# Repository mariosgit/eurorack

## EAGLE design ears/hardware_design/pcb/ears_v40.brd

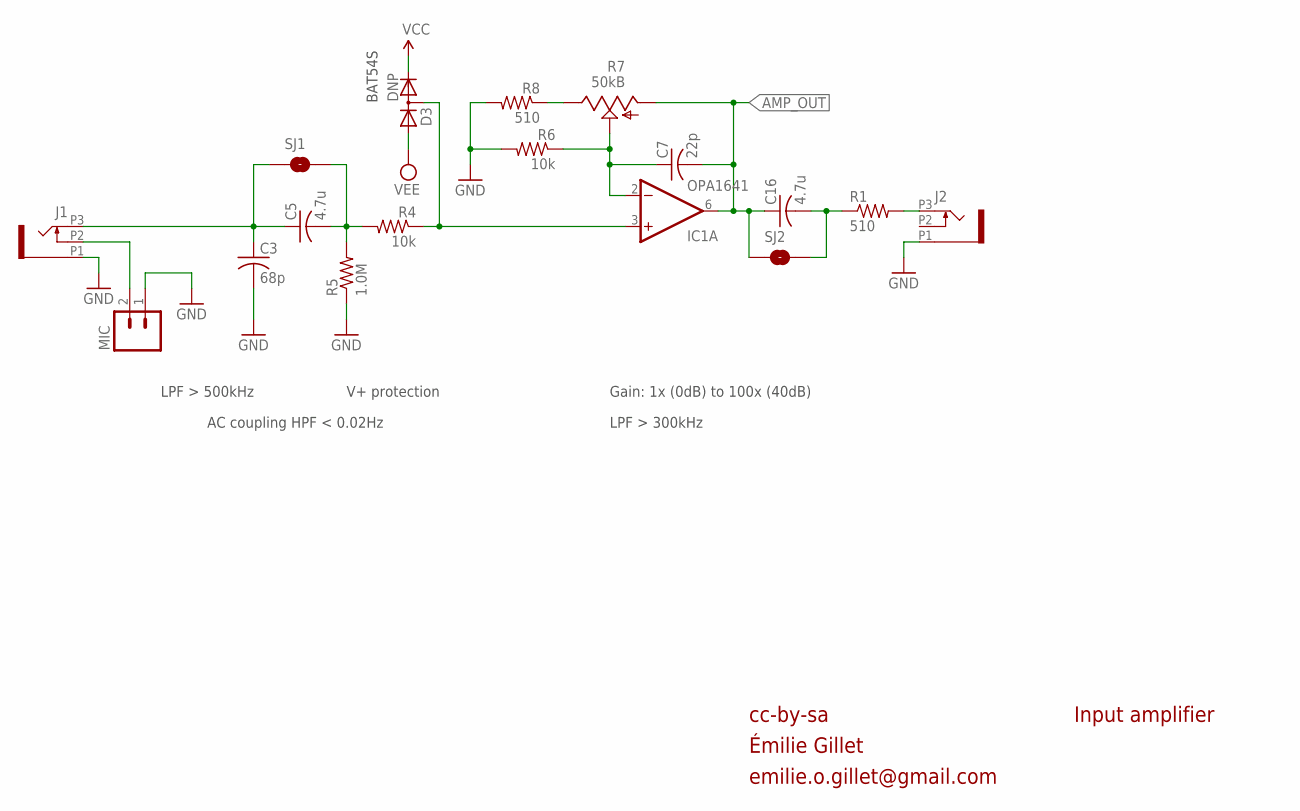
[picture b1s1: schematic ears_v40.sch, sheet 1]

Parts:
C3: 68p; C0402
C5, C16: 4.7u; C0603
C7: 22p; C0402
D3: DNP; SOT23
IC1: OPA1641; MSOP8
J1, J2: PJ301_THONKICONN6; WQP_PJ_301M6
MIC: M02TINY; 1X02_TINY
R1, R8: 510; R0402
R4, R6: 10k; R0402
R5: 1.0M; R0402
R7: 50kB; ALPS_POT_VERTICAL_PS
SJ1, SJ2: SOLDERJUMPERNC; SJ_2S

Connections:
AMP_OUT: C7.2, C16.1, IC1.6 (OUT), R7.P$3 (A), SJ2.1; also elsewhere on the board
GND: C3.2, J1.P1 (1), J2.P1 (1), MIC.1, R5.1, R6.2, R8.2; also elsewhere on the board
unnamed: D3.3 (AC), IC1.3 (+IN), R4.1
unnamed: J2.P3 (3), R1.2
unnamed: C3.1, C5.1, J1.P3 (3), SJ1.1
unnamed: J1.P2 (2), MIC.2
unnamed: C7.1, IC1.2 (-IN), R6.1, R7.P$2 (S)
unnamed: C5.2, R4.2, R5.2, SJ1.2
unnamed: R7.P$1 (E), R8.1
unnamed: C16.2, R1.1, SJ2.2
VCC: D3.2 (C); also elsewhere on the board
VEE: D3.1 (A); also elsewhere on the board

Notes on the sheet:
cc-by-sa
Input amplifier
Gain: 1x (0dB) to 100x (40dB)
LPF > 500kHz
V+ protection
LPF > 300kHz
AC coupling HPF < 0.02Hz
BAT54S
Émilie Gillet
emilie.o.gillet@gmail.com

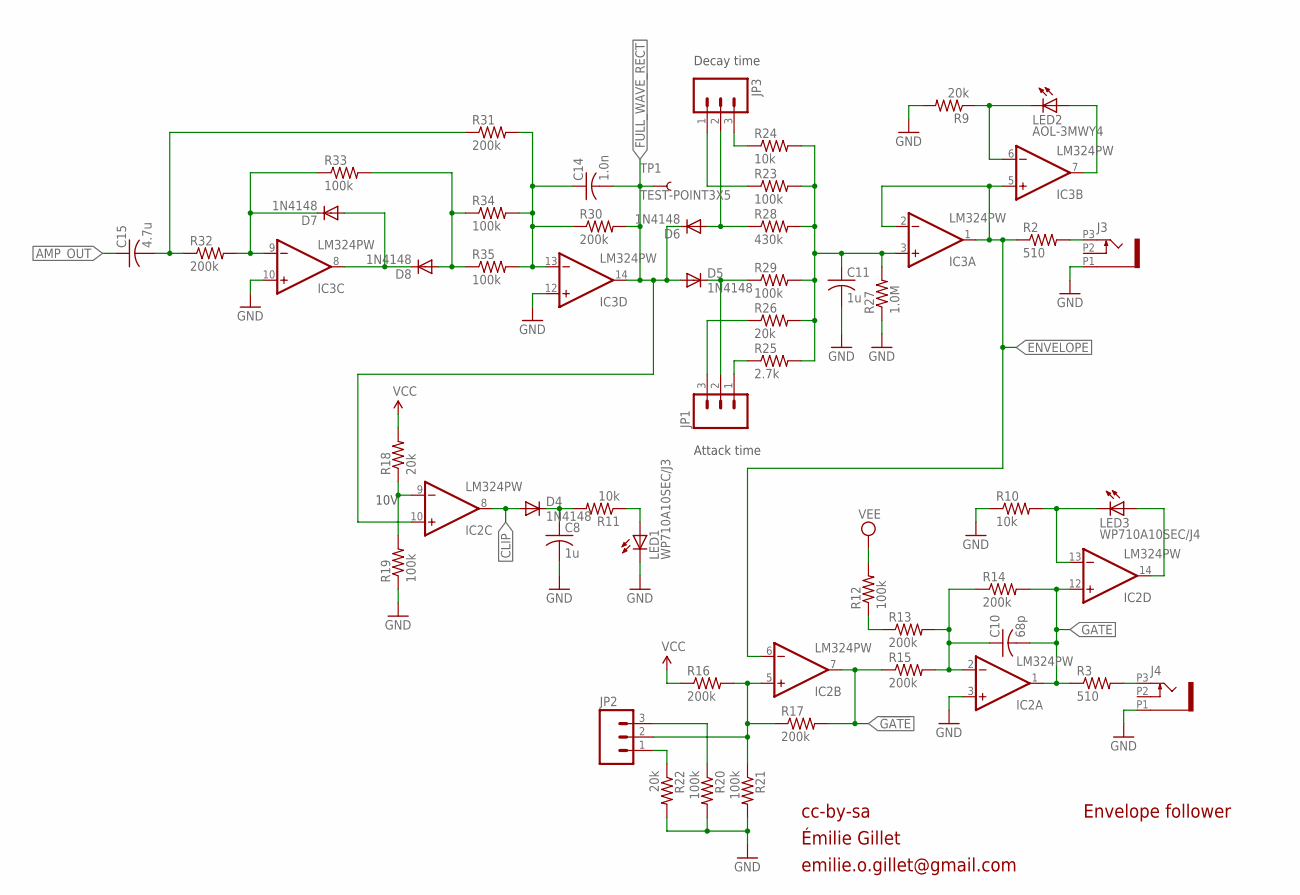
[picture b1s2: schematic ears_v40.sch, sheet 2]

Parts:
C8, C11: 1u; C0402
C10: 68p; C0402
C14: 1.0n; C0402
C15: 4.7u; C0603
D4, D5, D6, D7, D8: 1N4148; SOD523
IC2, IC3: LM324PW; TSSOP14
J3, J4: PJ301_THONKICONN6; WQP_PJ_301M6
JP1, JP2, JP3: M03PTH; 1X03
LED1: WP710A10SEC/J3; LED3MM
LED2: AOL-3MWY4; LED3MM
LED3: WP710A10SEC/J4; LED3MM
R2, R3: 510; R0402
R9, R18, R22, R26: 20k; R0402
R10, R11, R24: 10k; R0402
R12, R19, R20, R21, R23, R29, R33, R34, R35: 100k; R0402
R13, R14, R15, R16, R17, R30, R31, R32: 200k; R0402
R25: 2.7k; R0402
R27: 1.0M; R0402
R28: 430k; R0402
TP1: TEST-POINT3X5; PAD.03X.05

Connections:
!GATE: IC2.7 (OUT), R15.1, R17.2
AMP_OUT: C15.1; also elsewhere on the board
AMP_OUT_AC: C15.2, R31.1, R32.1
CLIP: D4.A, IC2.8 (OUT)
ENVELOPE: IC2.6 (-IN), IC3.1 (OUT), IC3.2 (-IN), IC3.5 (+IN), R2.1
FULL_WAVE_RECT: C14.2, D5.A, D6.C, IC2.10 (+IN), IC3.14 (OUT), R30.2, TP1.P$1
GATE: C10.2, IC2.1 (OUT), IC2.12 (+IN), R3.1, R14.2
GND: C8.2, C11.2, IC2.3 (+IN), IC3.10 (+IN), IC3.12 (+IN), J3.P1 (1), J4.P1 (1), LED1.K (C), R9.2, R10.1, R19.1, R20.2, R21.2, R22.2, R27.1; also elsewhere on the board
unnamed: D7.A, D8.C, IC3.8 (OUT)
unnamed: C10.1, IC2.2 (-IN), R13.2, R14.1, R15.2
unnamed: D7.C, IC3.9 (-IN), R32.2, R33.1
unnamed: D8.A, R33.2, R34.1, R35.1
unnamed: C14.1, IC3.13 (-IN), R30.1, R31.2, R34.2, R35.2
unnamed: J3.P3 (3), R2.2
unnamed: IC3.6 (-IN), LED2.K (C), R9.1
unnamed: D5.C, JP1.2, R29.1
unnamed: C11.1, IC3.3 (+IN), R23.2, R24.2, R25.2, R26.2, R27.2, R28.2, R29.2
unnamed: JP3.3, R24.1
unnamed: JP3.1, R23.1
unnamed: D6.A, JP3.2, R28.1
unnamed: JP1.1, R25.1
unnamed: JP1.3, R26.1
unnamed: IC2.9 (-IN), R18.1, R19.2
unnamed: C8.1, D4.C, R11.2
unnamed: IC3.7 (OUT), LED2.A
unnamed: LED1.A, R11.1
unnamed: J4.P3 (3), R3.2
unnamed: IC2.5 (+IN), JP2.2, R16.2, R17.1, R21.1
unnamed: JP2.1, R22.1
unnamed: JP2.3, R20.1
unnamed: IC2.13 (-IN), LED3.K (C), R10.2
unnamed: IC2.14 (OUT), LED3.A
unnamed: R12.1, R13.1
VCC: R16.1, R18.2; also elsewhere on the board
VEE: R12.2; also elsewhere on the board

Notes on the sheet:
cc-by-sa
Envelope follower
Decay time
Attack time
10V
Émilie Gillet
emilie.o.gillet@gmail.com

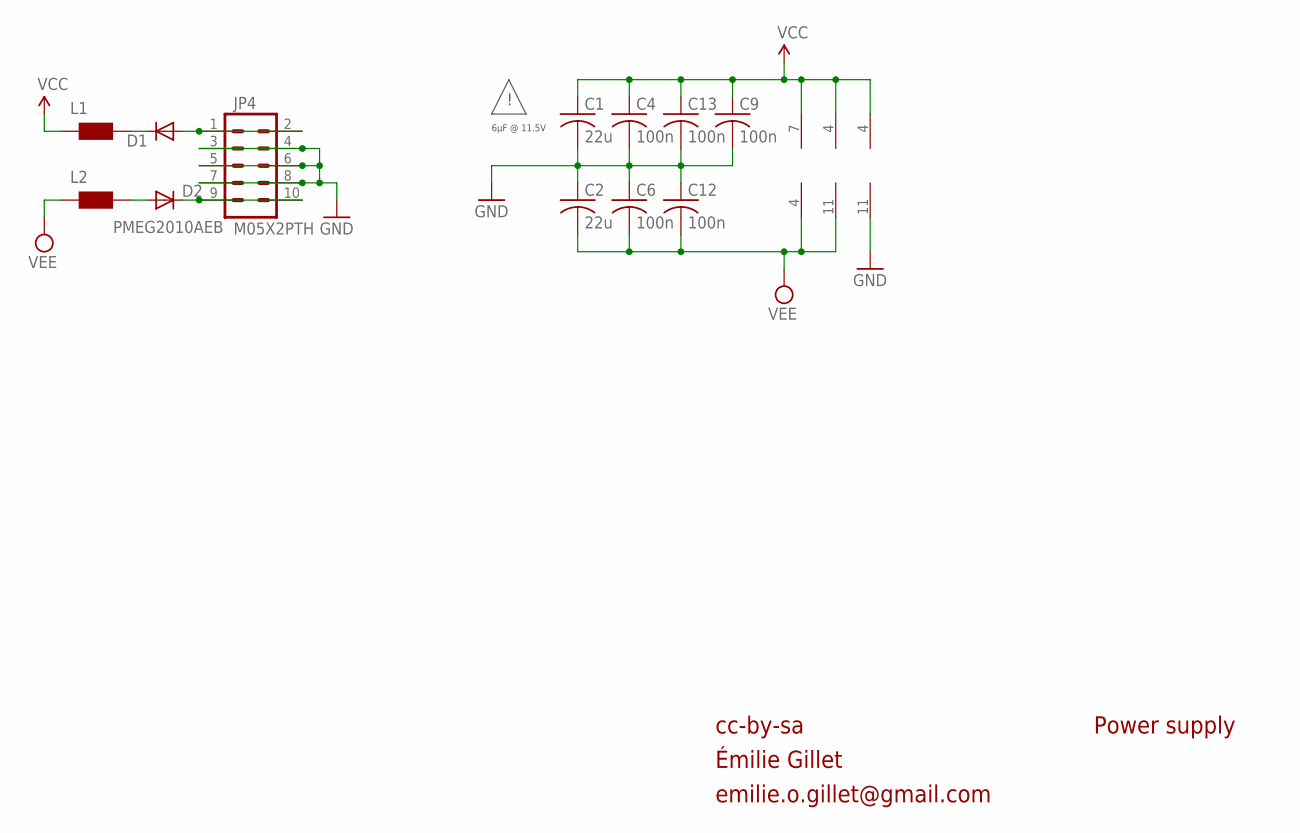
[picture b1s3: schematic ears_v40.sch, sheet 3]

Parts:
C1, C2: 22u; C1206
C4, C6, C9, C12, C13: 100n; C0402
D1, D2: PMEG2010AEB; SOD523
IC1: OPA1641; MSOP8
IC2, IC3: LM324PW; TSSOP14
JP4: M05X2PTH; AVR_ICSP
L1, L2: WE-CBF_0603; 0603

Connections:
GND: C1.2, C2.1, C4.2, C6.1, C9.2, C12.1, C13.2, IC2.11 (V-), JP4.3, JP4.4, JP4.5, JP4.6, JP4.7, JP4.8; also elsewhere on the board
unnamed: D1.A, JP4.1, JP4.2
unnamed: D2.C, JP4.9, JP4.10
unnamed: D1.C, L1.2
unnamed: D2.A, L2.2
VCC: C1.1, C4.1, C9.1, C13.1, IC1.7 (V+), IC2.4 (V+), IC3.4 (V+), L1.1; also elsewhere on the board
VEE: C2.2, C6.2, C12.2, IC1.4 (V-), IC3.11 (V-), L2.1; also elsewhere on the board

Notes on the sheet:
cc-by-sa
Power supply
6µF @ 11.5V
Émilie Gillet
emilie.o.gillet@gmail.com

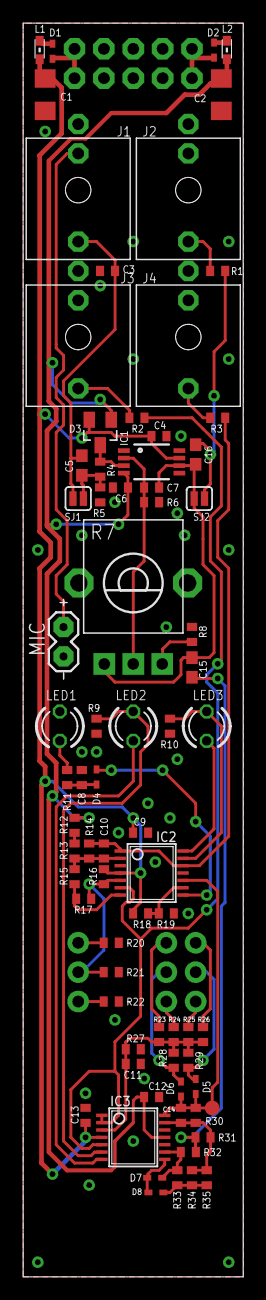
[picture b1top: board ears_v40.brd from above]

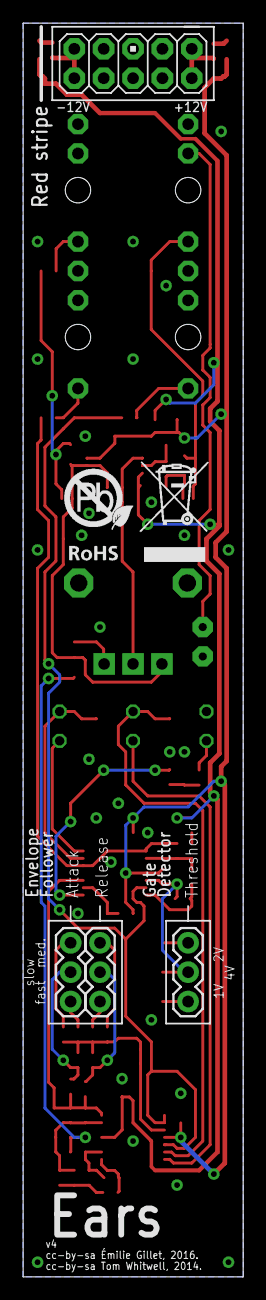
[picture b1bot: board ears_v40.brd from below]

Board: 2 copper layers, 19.0 x 108.4 mm, 80 parts (5 on the bottom side), 47 nets.

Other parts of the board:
U$2: ROHS

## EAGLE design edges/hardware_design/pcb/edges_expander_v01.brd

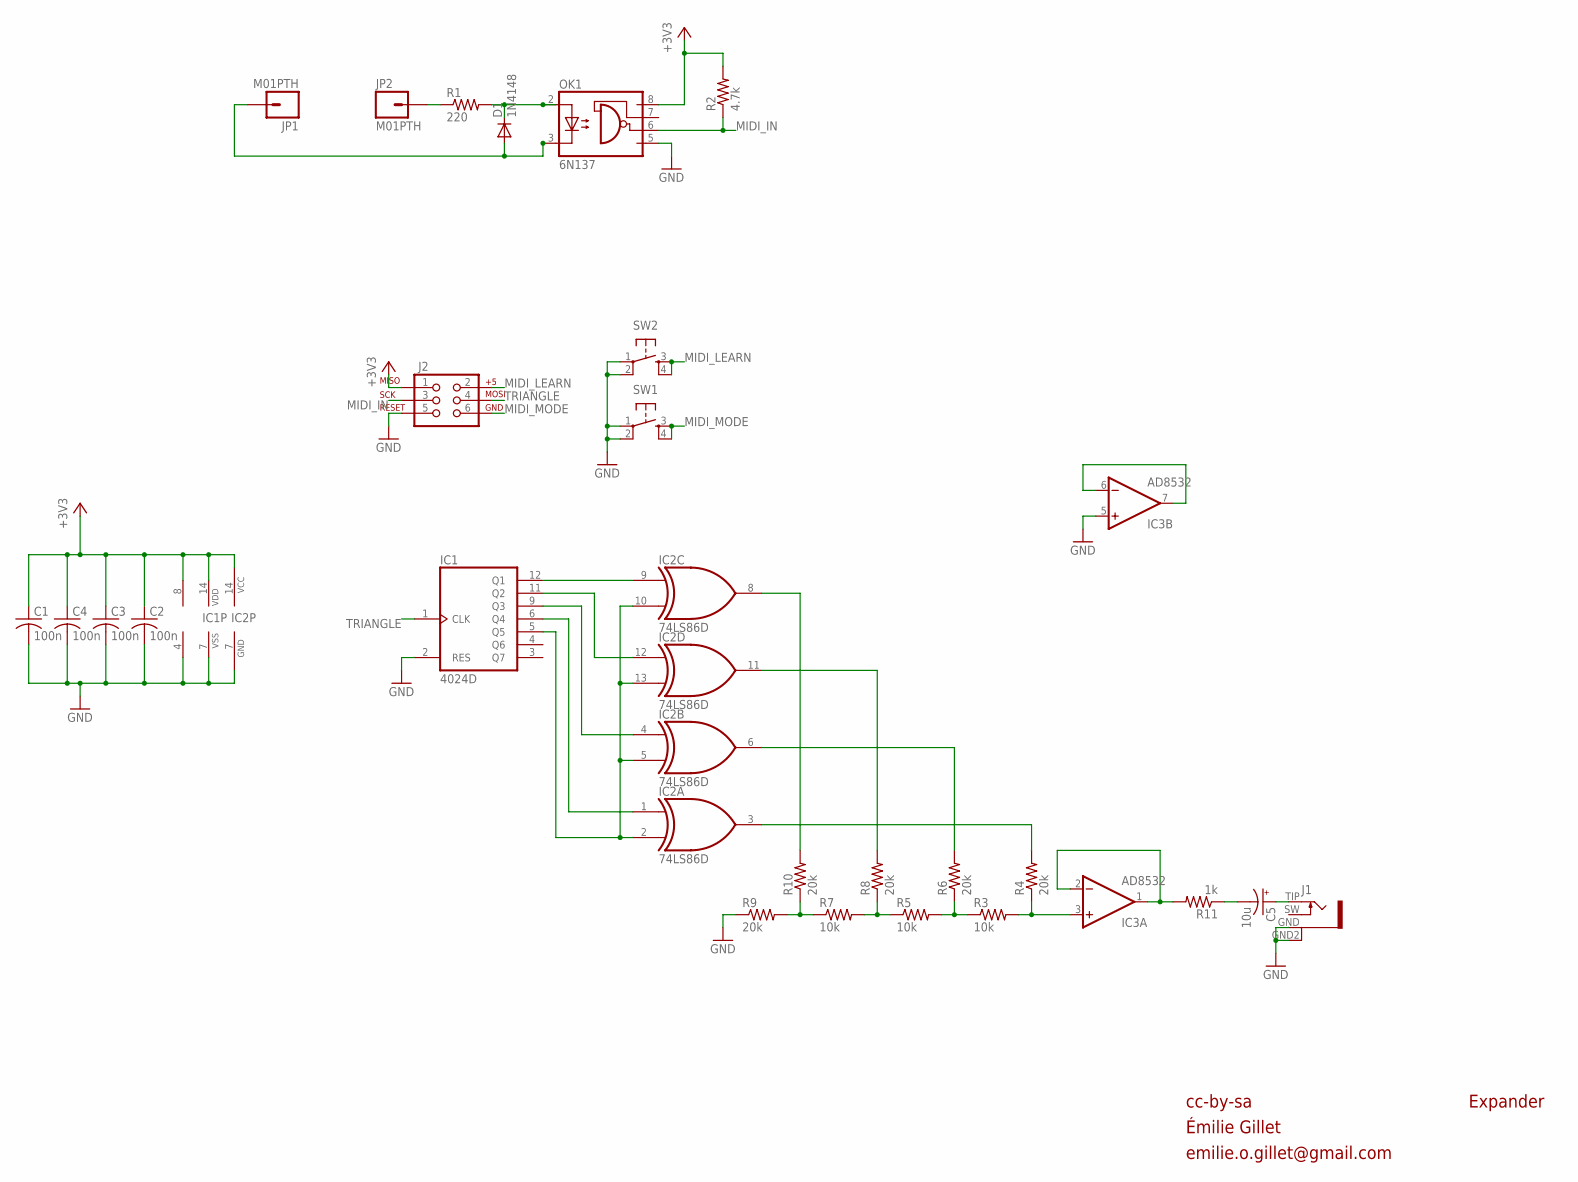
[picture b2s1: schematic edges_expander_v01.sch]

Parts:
C1, C2, C3, C4: 100n; C0603
C5: 10u; PANASONIC_B
D1: 1N4148; SOD323-W
IC1: 4024D; SO14
IC2: 74LS86D; SO14
IC3: AD8532; SO08
J1: PJ301WQP; WQP_PJ_301BM
J2: AVR_SPI_PRG_6PTH; 2X3
JP1, JP2: M01PTH; 1X01
OK1: 6N137; DIL8-SMD
R1: 220; R0603
R2: 4.7k; R0603
R3, R5, R7: 10k; R0603
R4, R6, R8, R9, R10: 20k; R0603
R11: 1k; R0603
SW1, SW2: TAC_SWITCHPTH; TACTILE-PTH

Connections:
+3V3_EXP: C1.1, C2.1, C3.1, C4.1, IC1.14 (VDD), IC2.14 (VCC), IC3.8 (V+), J2.1, OK1.8 (VCC), R2.2
GND: C1.2, C2.2, C3.2, C4.2, IC1.2 (RES), IC1.7 (VSS), IC2.7 (GND), IC3.4 (V-), IC3.5 (+IN), J1.GND (1), J1.GND2 (4), J2.5, OK1.5 (GND), R9.1, SW1.1, SW1.2, SW2.1, SW2.2
MIDI_IN: J2.3, OK1.6 (VO), R2.1
MIDI_IN4: JP2.1, R1.1
MIDI_IN5: D1.A, JP1.1, OK1.3 (C)
MIDI_LEARN: J2.2, SW2.3, SW2.4
MIDI_MODE: J2.6, SW1.3, SW1.4
unnamed: IC2.3 (O), R4.2
unnamed: IC2.6 (O), R6.2
unnamed: IC2.11 (O), R8.2
unnamed: IC2.8 (O), R10.2
unnamed: D1.C, OK1.2 (A), R1.2
unnamed: IC1.5 (Q5), IC2.2 (I1), IC2.5 (I1), IC2.10 (I1), IC2.13 (I1)
unnamed: IC1.9 (Q3), IC2.4 (I0)
unnamed: IC1.11 (Q2), IC2.12 (I0)
unnamed: IC1.12 (Q1), IC2.9 (I0)
unnamed: IC3.6 (-IN), IC3.7 (OUT)
unnamed: IC1.6 (Q4), IC2.1 (I0)
unnamed: R7.1, R9.2, R10.1
unnamed: R5.1, R7.2, R8.1
unnamed: R3.1, R5.2, R6.1
unnamed: IC3.3 (+IN), R3.2, R4.1
unnamed: C5.-, R11.1
unnamed: IC3.1 (OUT), IC3.2 (-IN), R11.2
unnamed: C5.+, J1.TIP (2)
TRIANGLE: IC1.1 (CLK), J2.4

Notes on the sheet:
cc-by-sa
Expander
Émilie Gillet
emilie.o.gillet@gmail.com

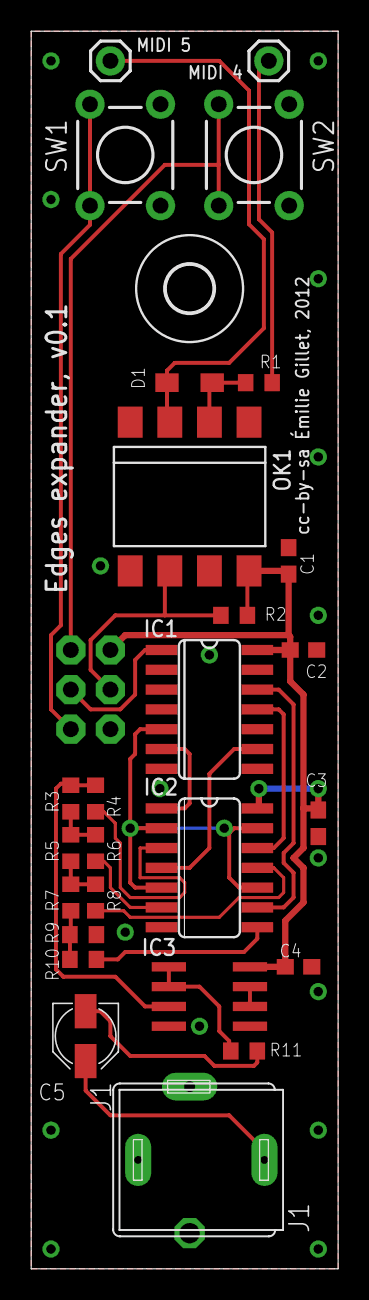
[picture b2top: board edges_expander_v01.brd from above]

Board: 2 copper layers, 19.7 x 79.4 mm, 28 parts (1 on the bottom side), 26 nets.

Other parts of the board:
U$1: 3,0

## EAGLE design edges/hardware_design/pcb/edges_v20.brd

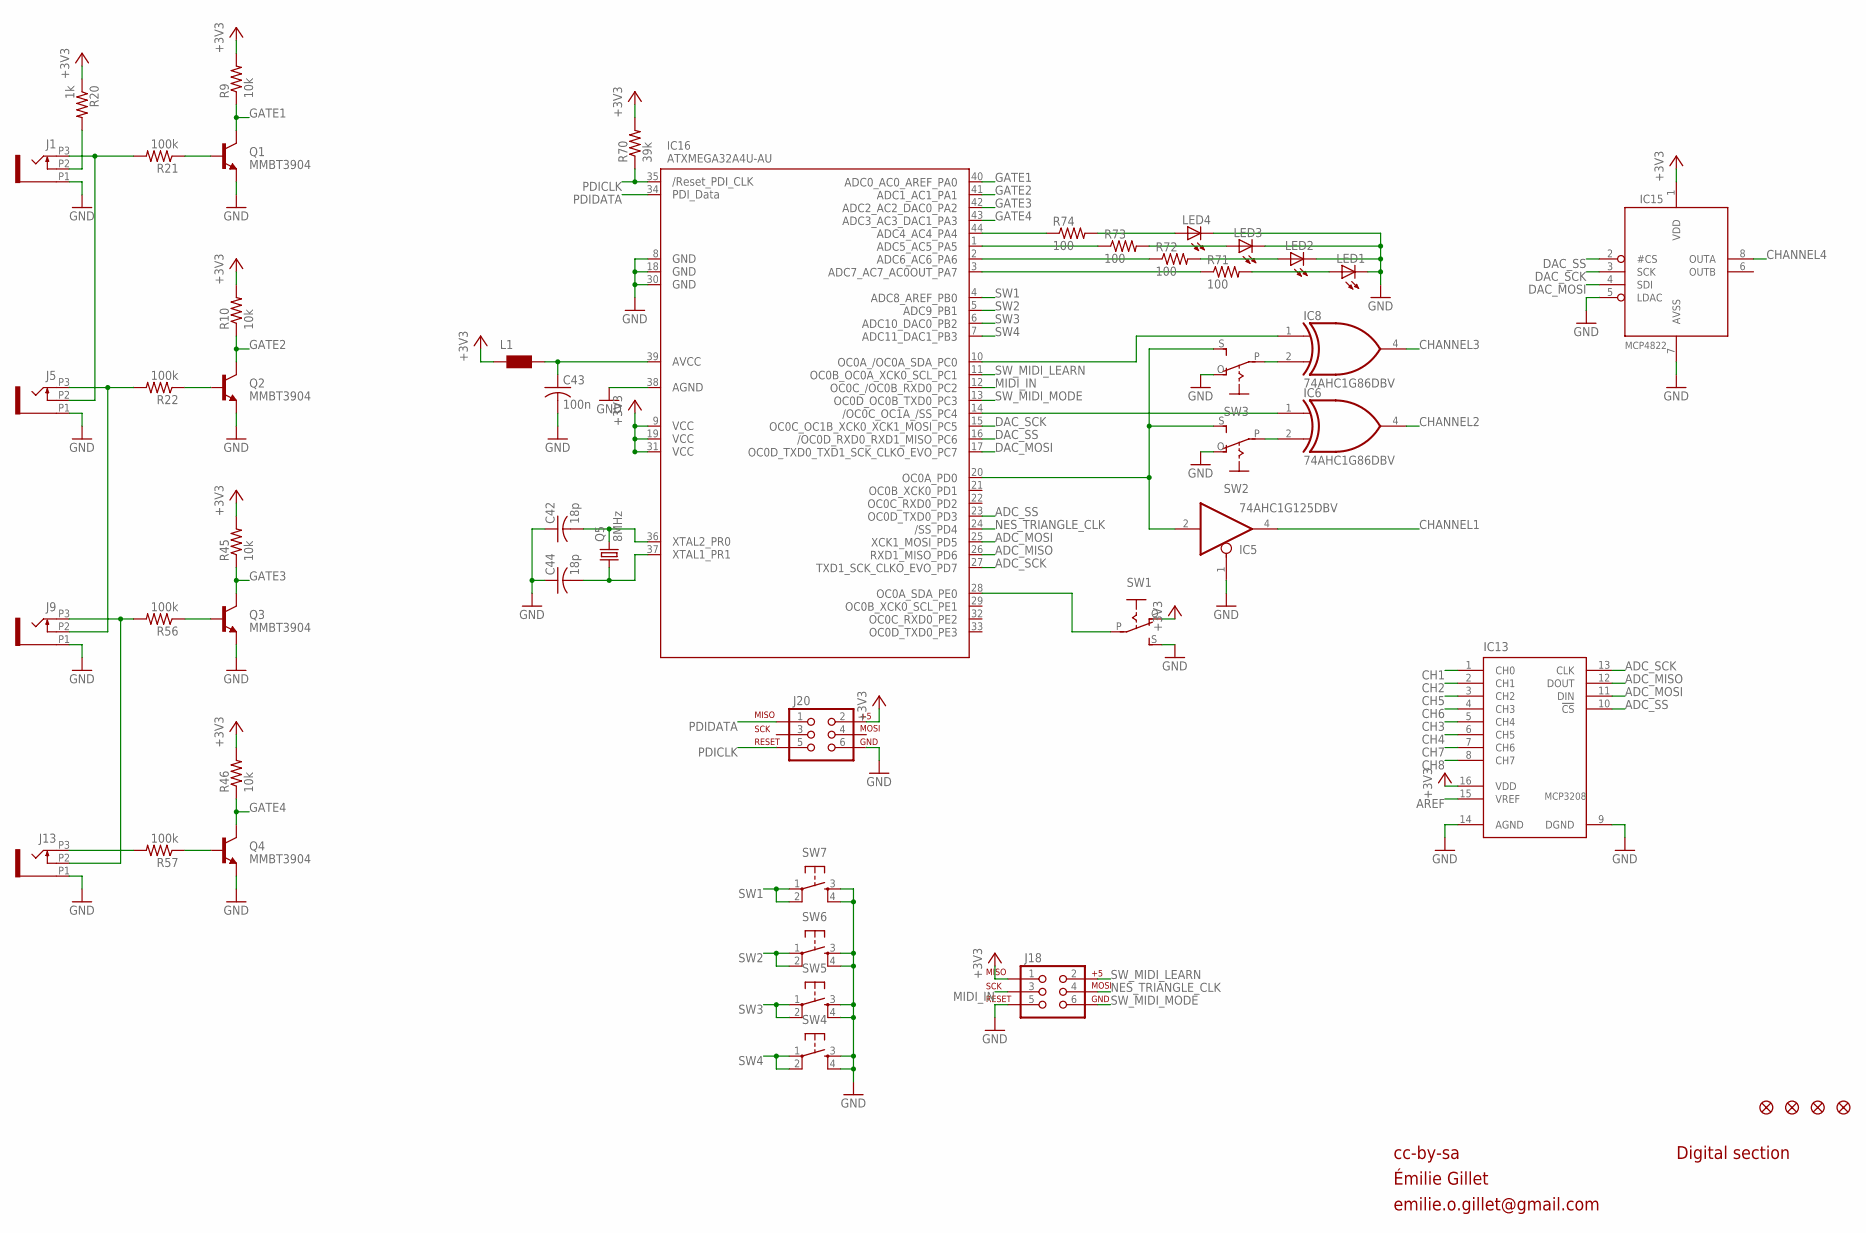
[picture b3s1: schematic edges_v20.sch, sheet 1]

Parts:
C42, C44: 18p; C0603
C43: 100n; C0603
IC5: 74AHC1G125DBV; SOT23-5
IC6, IC8: 74AHC1G86DBV; SOT23-5
IC13: MCP3208; SO16
IC15: MCP4822; SO08
IC16: ATXMEGA32A4U-AU; TQFP44
J1, J5, J9, J13: PJ301_THONKICONN6; WQP_PJ_301M6
J18, J20: AVR_SPI_PRG_6PTH; 2X3
JP1, JP2, JP3, JP4: FIDUCIAL1X2; FIDUCIAL-1X2
L1: WE-CBF_0603; 0603
LED1, LED2, LED3, LED4: LED3MM
Q1, Q2, Q3, Q4: MMBT3904; SOT23-BEC
Q5: 8MHz; HC49U70
R9, R10, R45, R46: 10k; R0603
R20: 1k; R0603
R21, R22, R56, R57: 100k; R0603
R70: 39k; R0603
R71, R72, R73, R74: 100; R0603
SW1, SW2, SW3: S-ON-ONSMALL_SLIDE; ES_100SP1T6B11M2QEH_SMALL
SW4, SW5, SW6, SW7: TAC_SWITCHPTH; TACTILE-PTH

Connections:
+3V3: IC13.16 (VDD), IC15.1 (VDD), IC16.9 (VCC1), IC16.19 (VCC2), IC16.31 (VCC3), J18.1, J20.2, L1.1, R9.2, R10.2, R20.1, R45.2, R46.2, R70.2, SW1.O; also elsewhere on the board
ADC_MISO: IC13.12 (DOUT), IC16.26 (PD6)
ADC_MOSI: IC13.11 (DIN), IC16.25 (PD5)
ADC_SCK: IC13.13 (CLK), IC16.27 (PD7)
ADC_SS: IC13.10 (!CS), IC16.23 (PD3)
AREF: IC13.15 (VREF); also elsewhere on the board
CH1: IC13.1 (CH0); also elsewhere on the board
CH2: IC13.2 (CH1); also elsewhere on the board
CH3: IC13.5 (CH4); also elsewhere on the board
CH4: IC13.6 (CH5); also elsewhere on the board
CH5: IC13.3 (CH2); also elsewhere on the board
CH6: IC13.4 (CH3); also elsewhere on the board
CH7: IC13.7 (CH6); also elsewhere on the board
CH8: IC13.8 (CH7); also elsewhere on the board
CHANNEL1: IC5.4 (O); also elsewhere on the board
CHANNEL2: IC6.4 (O); also elsewhere on the board
CHANNEL3: IC8.4 (O); also elsewhere on the board
CHANNEL4: IC15.8 (OUTA); also elsewhere on the board
DAC_MOSI: IC15.4 (SDI), IC16.17 (PC7)
DAC_SCK: IC15.3 (SCK), IC16.15 (PC5)
DAC_SS: IC15.2 (#CS), IC16.16 (PC6)
GATE1: IC16.40 (PA0), Q1.C, R9.1
GATE1_IN: J1.P3 (3), J5.P2 (2), R21.2
GATE1_LED: LED4.A, R74.2
GATE2: IC16.41 (PA1), Q2.C, R10.1
GATE2_IN: J5.P3 (3), J9.P2 (2), R22.2
GATE2_LED: LED3.A, R73.2
GATE3: IC16.42 (PA2), Q3.C, R45.1
GATE3_IN: J9.P3 (3), J13.P2 (2), R56.2
GATE3_LED: LED2.A, R72.2
GATE4: IC16.43 (PA3), Q4.C, R46.1
GATE4_IN: J13.P3 (3), R57.2
GATE4_LED: LED1.A, R71.2
GND: C42.1, C43.2, C44.1, IC5.1 (OE), IC13.9 (DGND), IC13.14 (AGND), IC15.5 (LDAC), IC15.7 (AVSS), IC16.8 (GND1), IC16.18 (GND2), IC16.30 (GND3), IC16.38 (AGND), J1.P1 (1), J5.P1 (1), J9.P1 (1), J13.P1 (1), J18.5, J20.6, LED1.K (C), LED2.K (C), LED3.K (C), LED4.K (C), Q1.E, Q2.E, Q3.E, Q4.E, SW1.S, SW2.O, SW3.O, SW4.3, SW4.4, SW5.3, SW5.4, SW6.3, SW6.4, SW7.3, SW7.4; also elsewhere on the board
MIDI_IN: IC16.12 (PC2), J18.3
unnamed: Q1.B, R21.1
unnamed: Q2.B, R22.1
unnamed: Q3.B, R56.1
unnamed: IC16.44 (PA4), R74.1
unnamed: IC16.1 (PA5), R73.1
unnamed: IC16.2 (PA6), R72.1
unnamed: IC16.3 (PA7), R71.1
unnamed: J1.P2 (2), R20.2
unnamed: IC6.1 (I0), IC16.14 (PC4)
unnamed: IC8.2 (I1), SW3.P
unnamed: IC6.2 (I1), SW2.P
unnamed: C43.1, IC16.39 (AVCC), L1.2
unnamed: IC8.1 (I0), IC16.10 (PC0)
unnamed: IC5.2 (I), IC16.20 (PD0), SW2.S, SW3.S
unnamed: C44.2, IC16.37 (PR1), Q5.1
unnamed: C42.2, IC16.36 (PR0), Q5.2
unnamed: Q4.B, R57.1
NES_TRIANGLE_CLK: IC16.24 (PD4), J18.4
PDICLK: IC16.35 (RESET), J20.5, R70.1
PDIDATA: IC16.34 (PDI_DATA), J20.1
SW1: IC16.4 (PB0), SW7.1, SW7.2
SW2: IC16.5 (PB1), SW6.1, SW6.2
SW3: IC16.6 (PB2), SW5.1, SW5.2
SW4: IC16.7 (PB3), SW4.1, SW4.2
SW_MIDI_LEARN: IC16.11 (PC1), J18.2
SW_MIDI_MODE: IC16.13 (PC3), J18.6
SYNC_SWITCH: IC16.28 (PE0), SW1.P

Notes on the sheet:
cc-by-sa
Digital section
Émilie Gillet
emilie.o.gillet@gmail.com

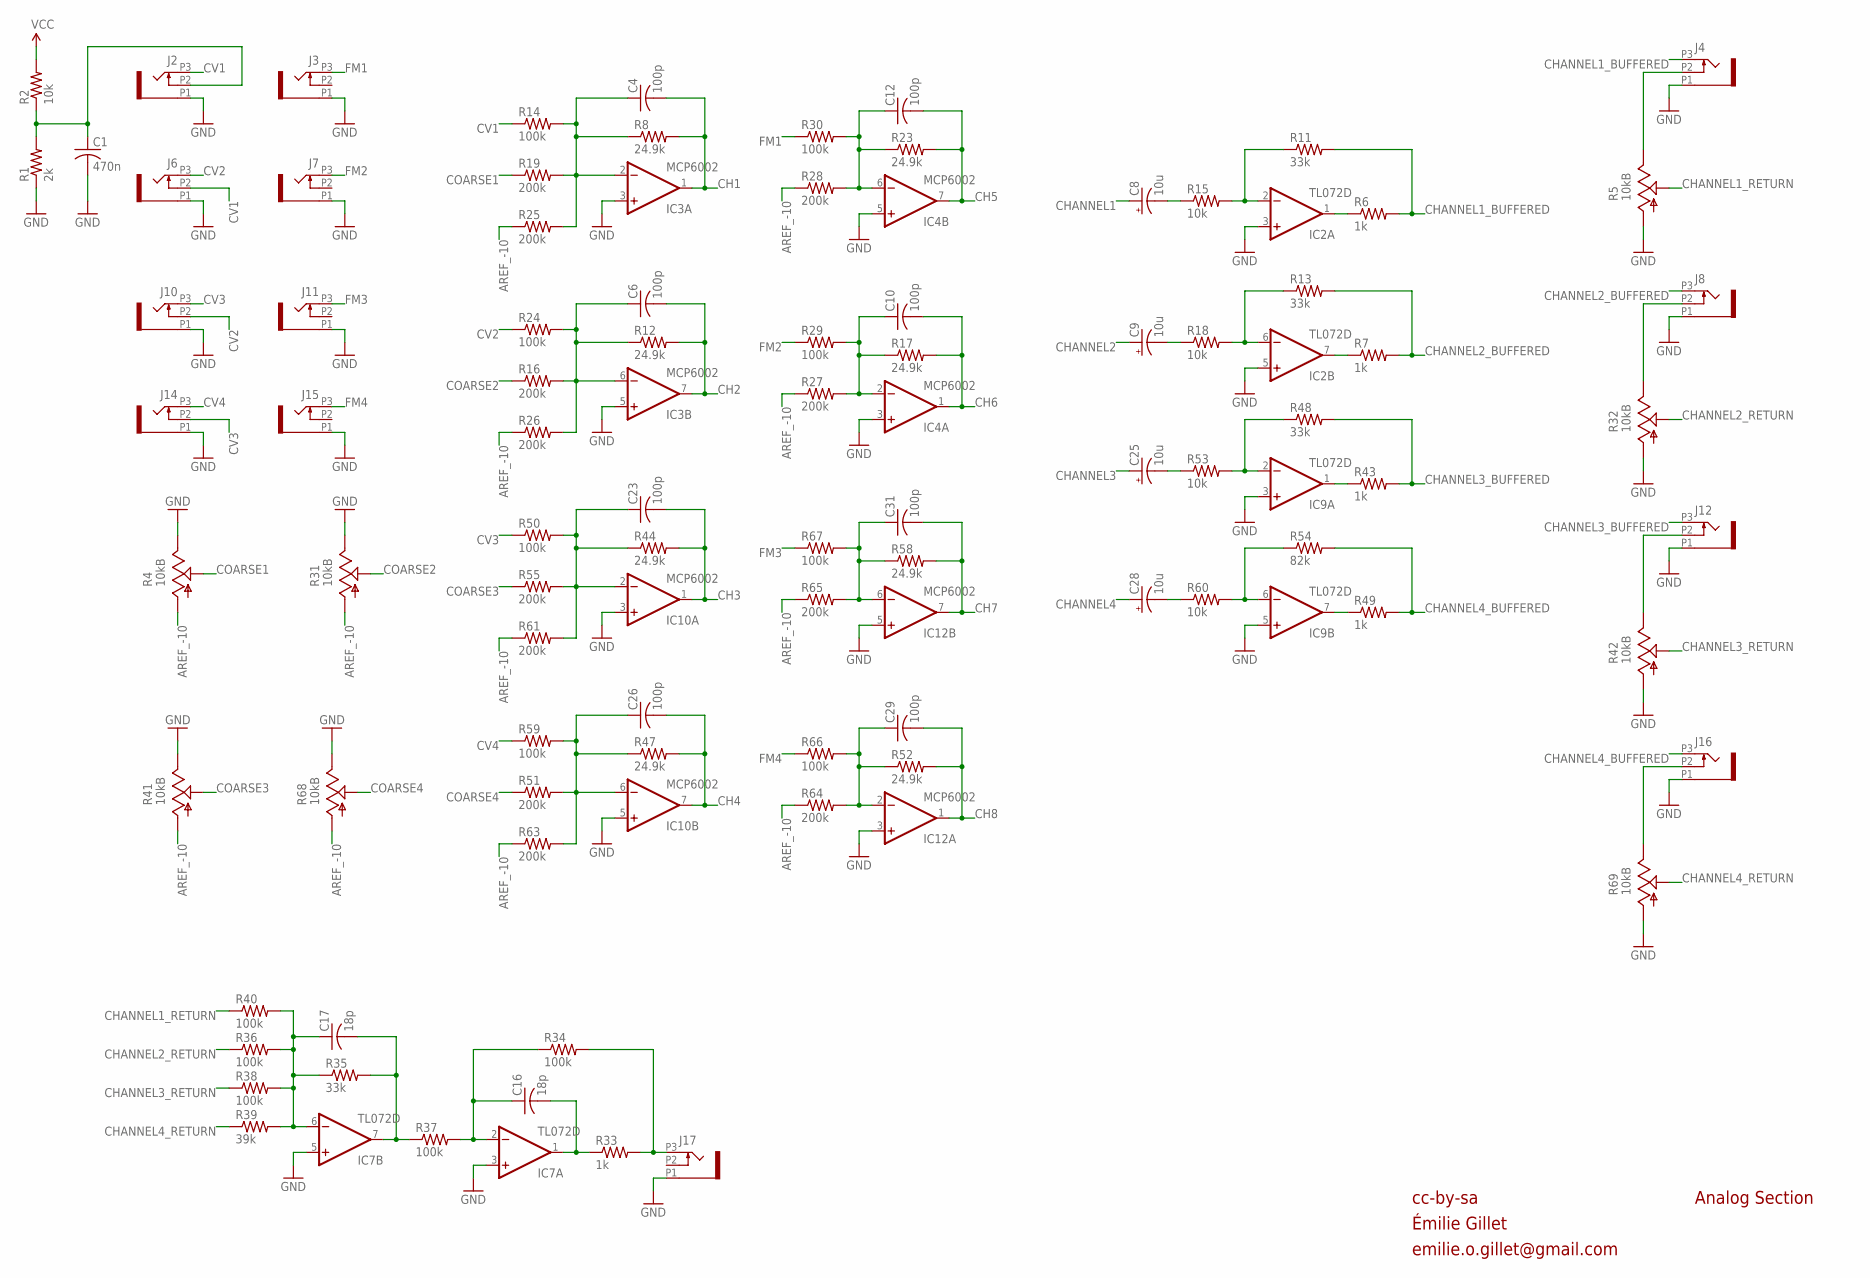
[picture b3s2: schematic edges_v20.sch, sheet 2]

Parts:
C1: 470n; C0603
C4, C6, C10, C12, C23, C26, C29, C31: 100p; C0603
C8, C9, C25, C28: 10u; PANASONIC_B
C16, C17: 18p; C0603
IC2, IC7, IC9: TL072D; SO08
IC3, IC4, IC10, IC12: MCP6002; SO08
J2, J3, J4, J6, J7, J8, J10, J11, J12, J14, J15, J16, J17: PJ301_THONKICONN6; WQP_PJ_301M6
R1: 2k; R0603
R2, R15, R18, R53, R60: 10k; R0603
R4, R5, R31, R32, R41, R42, R68, R69: 10kB; ALPS_POT_VERTICAL_PS
R6, R7, R33, R43, R49: 1k; R0603
R8, R12, R17, R23, R44, R47, R52, R58: 24.9k; R0603
R11, R13, R35, R48: 33k; R0603
R14, R24, R29, R30, R34, R36, R37, R38, R40, R50, R59, R66, R67: 100k; R0603
R16, R19, R25, R26, R27, R28, R51, R55, R61, R63, R64, R65: 200k; R0603
R39: 39k; R0603
R54: 82k; R0603

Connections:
AREF_-10: R4.P$3 (A), R25.1, R26.1, R27.1, R28.1, R31.P$3 (A), R41.P$3 (A), R61.1, R63.1, R64.1, R65.1, R68.P$3 (A); also elsewhere on the board
CH1: C4.2, IC3.1 (OUT), R8.2; also elsewhere on the board
CH2: C6.2, IC3.7 (OUT), R12.2; also elsewhere on the board
CH3: C23.2, IC10.1 (OUT), R44.2; also elsewhere on the board
CH4: C26.2, IC10.7 (OUT), R47.2; also elsewhere on the board
CH5: C12.2, IC4.7 (OUT), R23.2; also elsewhere on the board
CH6: C10.2, IC4.1 (OUT), R17.2; also elsewhere on the board
CH7: C31.2, IC12.7 (OUT), R58.2; also elsewhere on the board
CH8: C29.2, IC12.1 (OUT), R52.2; also elsewhere on the board
CHANNEL1: C8.+; also elsewhere on the board
CHANNEL1_BUFFERED: J4.P3 (3), R6.2, R11.2
CHANNEL1_RETURN: R5.P$2 (S), R40.1
CHANNEL2: C9.+; also elsewhere on the board
CHANNEL2_BUFFERED: J8.P3 (3), R7.2, R13.2
CHANNEL2_RETURN: R32.P$2 (S), R36.1
CHANNEL3: C25.+; also elsewhere on the board
CHANNEL3_BUFFERED: J12.P3 (3), R43.2, R48.2
CHANNEL3_RETURN: R38.1, R42.P$2 (S)
CHANNEL4: C28.+; also elsewhere on the board
CHANNEL4_BUFFERED: J16.P3 (3), R49.2, R54.2
CHANNEL4_RETURN: R39.1, R69.P$2 (S)
COARSE1: R4.P$2 (S), R19.1
COARSE2: R16.1, R31.P$2 (S)
COARSE3: R41.P$2 (S), R55.1
COARSE4: R51.1, R68.P$2 (S)
CV1: J2.P3 (3), J6.P2 (2), R14.1
CV2: J6.P3 (3), J10.P2 (2), R24.1
CV3: J10.P3 (3), J14.P2 (2), R50.1
CV4: J14.P3 (3), R59.1
FM1: J3.P3 (3), R30.1
FM2: J7.P3 (3), R29.1
FM3: J11.P3 (3), R67.1
FM4: J15.P3 (3), R66.1
GND: C1.2, IC2.3 (+IN), IC2.5 (+IN), IC3.3 (+IN), IC3.5 (+IN), IC4.3 (+IN), IC4.5 (+IN), IC7.3 (+IN), IC7.5 (+IN), IC9.3 (+IN), IC9.5 (+IN), IC10.3 (+IN), IC10.5 (+IN), IC12.3 (+IN), IC12.5 (+IN), J2.P1 (1), J3.P1 (1), J4.P1 (1), J6.P1 (1), J7.P1 (1), J8.P1 (1), J10.P1 (1), J11.P1 (1), J12.P1 (1), J14.P1 (1), J15.P1 (1), J16.P1 (1), J17.P1 (1), R1.1, R4.P$1 (E), R5.P$3 (A), R31.P$1 (E), R32.P$3 (A), R41.P$1 (E), R42.P$3 (A), R68.P$1 (E), R69.P$3 (A); also elsewhere on the board
MIX: J17.P3 (3), R33.2, R34.2
unnamed: J8.P2 (2), R32.P$1 (E)
unnamed: C23.1, IC10.2 (-IN), R44.1, R50.2, R55.2, R61.2
unnamed: C10.1, IC4.2 (-IN), R17.1, R27.2, R29.2
unnamed: C26.1, IC10.6 (-IN), R47.1, R51.2, R59.2, R63.2
unnamed: C31.1, IC12.6 (-IN), R58.1, R65.2, R67.2
unnamed: C29.1, IC12.2 (-IN), R52.1, R64.2, R66.2
unnamed: C8.-, R15.1
unnamed: IC2.2 (-IN), R11.1, R15.2
unnamed: IC2.1 (OUT), R6.1
unnamed: C9.-, R18.1
unnamed: IC2.6 (-IN), R13.1, R18.2
unnamed: IC2.7 (OUT), R7.1
unnamed: C25.-, R53.1
unnamed: C12.1, IC4.6 (-IN), R23.1, R28.2, R30.2
unnamed: IC9.2 (-IN), R48.1, R53.2
unnamed: IC9.1 (OUT), R43.1
unnamed: C28.-, R60.1
unnamed: IC9.6 (-IN), R54.1, R60.2
unnamed: IC9.7 (OUT), R49.1
unnamed: C17.1, IC7.6 (-IN), R35.1, R36.2, R38.2, R39.2, R40.2
unnamed: C16.1, IC7.2 (-IN), R34.1, R37.2
unnamed: C16.2, IC7.1 (OUT), R33.1
unnamed: J4.P2 (2), R5.P$1 (E)
unnamed: C17.2, IC7.7 (OUT), R35.2, R37.1
unnamed: J12.P2 (2), R42.P$1 (E)
unnamed: J16.P2 (2), R69.P$1 (E)
unnamed: C6.1, IC3.6 (-IN), R12.1, R16.2, R24.2, R26.2
unnamed: C1.1, J2.P2 (2), R1.2, R2.1
unnamed: C4.1, IC3.2 (-IN), R8.1, R14.2, R19.2, R25.2
VCC: R2.2; also elsewhere on the board

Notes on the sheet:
cc-by-sa
Analog Section
Émilie Gillet
emilie.o.gillet@gmail.com

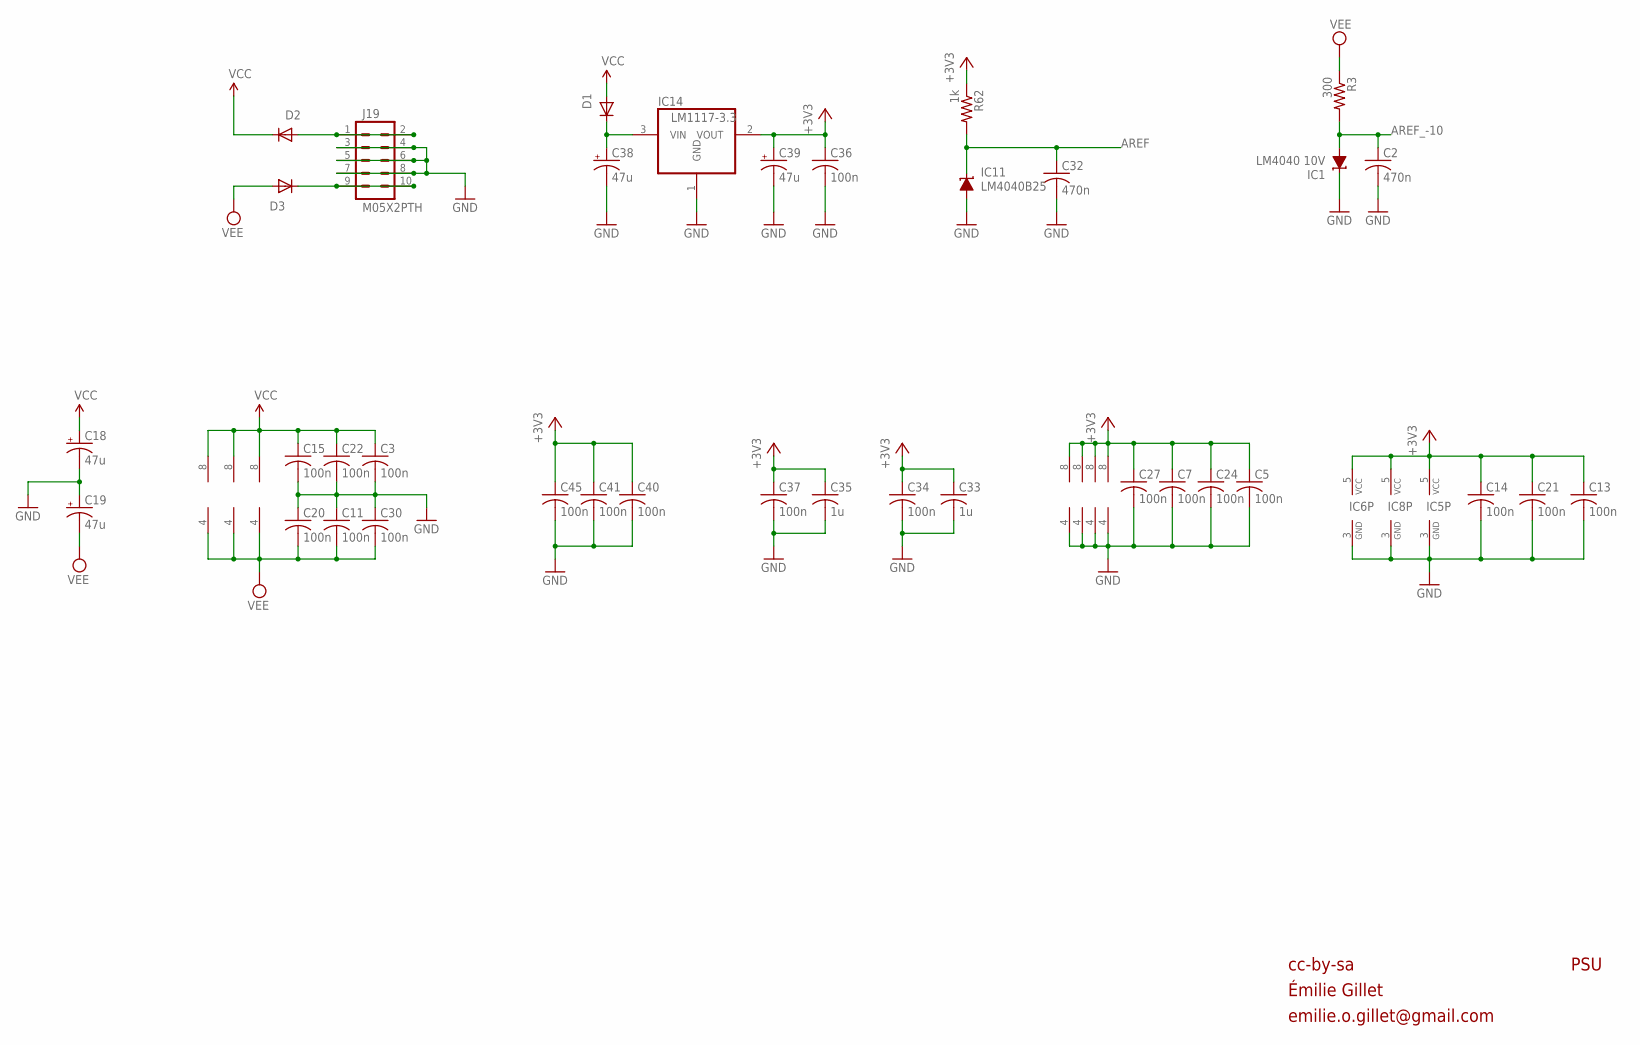
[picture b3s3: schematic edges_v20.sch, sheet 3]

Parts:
C2, C32: 470n; C0603
C3, C5, C7, C11, C13, C14, C15, C20, C21, C22, C24, C27, C30, C34, C36, C37, C40, C41, C45: 100n; C0603
C18, C19, C38, C39: 47u; PANASONIC_D
C33, C35: 1u; C0603
D1, D2, D3: 1N5819HW; SOD123
IC1: LM4040 10V; DBZ_R-PDSO-G3
IC2, IC7, IC9: TL072D; SO08
IC3, IC4, IC10, IC12: MCP6002; SO08
IC5: 74AHC1G125DBV; SOT23-5
IC6, IC8: 74AHC1G86DBV; SOT23-5
IC11: LM4040B25; DBZ_R-PDSO-G3
IC14: LM1117-3.3; SOT223
J19: M05X2PTH; AVR_ICSP
R3: 300; R0603
R62: 1k; R0603

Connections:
+3V3: C5.1, C7.1, C13.1, C14.1, C21.1, C24.1, C27.1, C33.1, C34.1, C35.1, C36.1, C37.1, C39.+, C40.1, C41.1, C45.1, IC3.8 (V+), IC4.8 (V+), IC5.5 (VCC), IC6.5 (VCC), IC8.5 (VCC), IC10.8 (V+), IC12.8 (V+), IC14.2 (VOUT), R62.1; also elsewhere on the board
AREF: C32.1, IC11.1 (C), R62.2; also elsewhere on the board
AREF_-10: C2.1, IC1.2 (A), R3.2; also elsewhere on the board
GND: C2.2, C3.2, C5.2, C7.2, C11.1, C13.2, C14.2, C15.2, C18.-, C19.+, C20.1, C21.2, C22.2, C24.2, C27.2, C30.1, C32.2, C33.2, C34.2, C35.2, C36.2, C37.2, C38.-, C39.-, C40.2, C41.2, C45.2, IC1.1 (C), IC3.4 (V-), IC4.4 (V-), IC5.3 (GND), IC6.3 (GND), IC8.3 (GND), IC10.4 (V-), IC11.2 (A), IC12.4 (V-), IC14.1 (GND), J19.3, J19.4, J19.5, J19.6, J19.7, J19.8; also elsewhere on the board
unnamed: C38.+, D1.C, IC14.3 (VIN)
unnamed: D2.A, J19.1, J19.2
unnamed: D3.C, J19.9, J19.10
VCC: C3.1, C15.1, C18.+, C22.1, D1.A, D2.C, IC2.8 (V+), IC7.8 (V+), IC9.8 (V+); also elsewhere on the board
VEE: C11.2, C19.-, C20.2, C30.2, D3.A, IC2.4 (V-), IC7.4 (V-), IC9.4 (V-), R3.1

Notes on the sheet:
cc-by-sa
PSU
Émilie Gillet
emilie.o.gillet@gmail.com

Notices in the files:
ears/hardware_design/pcb/ears_v40.brd:
cc-by-sa Émilie Gillet, 2016.
cc-by-sa Tom Whitwell, 2014.
edges/hardware_design/pcb/edges_expander_v01.brd:
cc-by-sa Émilie Gillet, 2012
edges/hardware_design/pcb/edges_v20.brd:
cc-by-sa Émilie Gillet, 2014. v2
frames/hardware_design/pcb/frames_v03.brd:
cc-by-sa Émilie Gillet, 2013. v0.3
